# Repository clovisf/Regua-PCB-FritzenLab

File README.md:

# Regua-PCB-FritzenLab
 Regua 20cm feita em circuito impresso

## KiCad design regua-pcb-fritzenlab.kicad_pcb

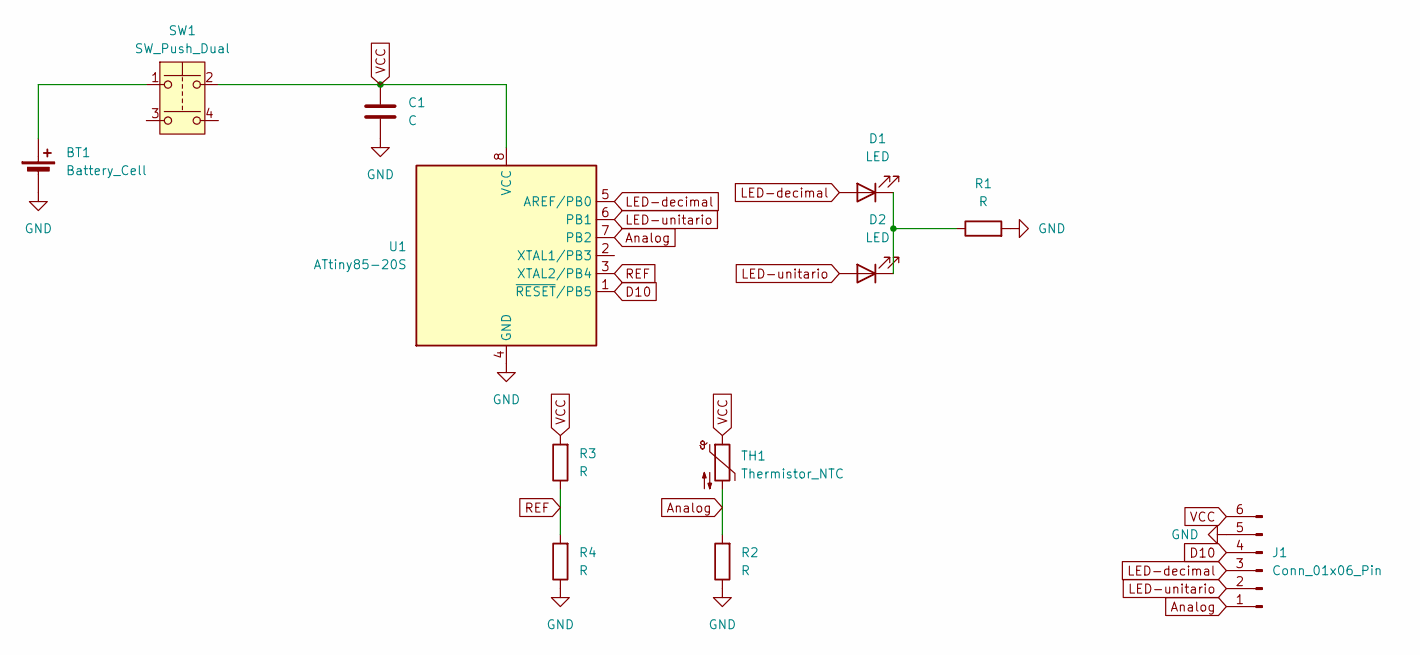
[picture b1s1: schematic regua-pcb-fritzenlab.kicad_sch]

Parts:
BT1: Battery_Cell; BatteryHolder_Multicomp_BC-2001_1x2032
C1: C; C_0805_2012Metric
D1, D2: LED; LED_0805_2012Metric
J1: Conn_01x06_Pin; PinHeader_1x06_P2.54mm_Vertical
R1, R2, R3, R4: R; R_0805_2012Metric
SW1: SW_Push_Dual; SW_SPST_B3S-1000
TH1: Thermistor_NTC; R_0805_2012Metric
U1: ATtiny85-20S; SOIC-8W_5.3x5.3mm_P1.27mm

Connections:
Analog: J1.1, R2.2, TH1.2, U1.7 (PB2)
D10: J1.4, U1.1 (~RESET/PB5)
GND: BT1.2 (-), C1.2, J1.5, R1.2, R2.1, R4.1, U1.4 (GND)
LED-decimal: D1.2 (A), J1.3, U1.5 (AREF/PB0)
LED-unitario: D2.2 (A), J1.2, U1.6 (PB1)
unnamed: BT1.1 (+), SW1.1
unnamed: D1.1 (K), D2.1 (K), R1.1
REF: R3.1, R4.2, U1.3 (XTAL2/PB4)
VCC: C1.1, J1.6, R3.2, SW1.2, TH1.1, U1.8 (VCC)

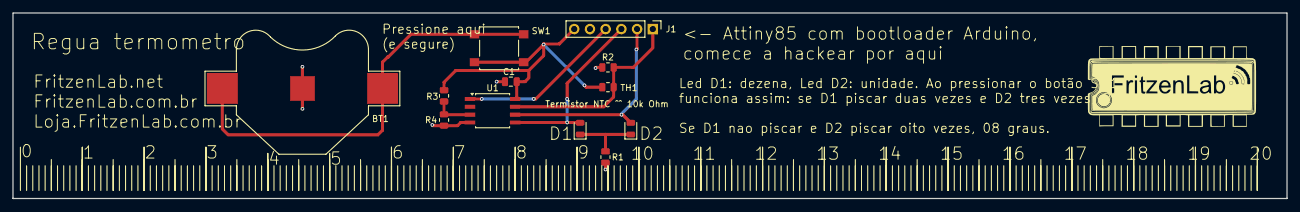
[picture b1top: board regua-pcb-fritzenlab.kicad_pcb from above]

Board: 2 copper layers, 206.0 x 30.0 mm, 12 parts (0 on the bottom side), 9 nets.

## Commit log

2024-11-02 finished design, gerbers generated
2024-11-02 Adicionada imagem da régua 3D
2024-11-03 backups
2024-12-19 mostly finished coding
2024-12-29 edited code
    Edited code to turn LEDs off after every cycle
2025-01-14 edited code
